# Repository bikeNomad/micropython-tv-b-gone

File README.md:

# MicroPython TV-B-Gone clone
## Introduction
This is a MicroPython implementation of the TV-B-Gone project.
The [TV-B-Gone](https://www.tvbgone.com/) (by Mitch Altman) is a universal remote control that can turn off most televisions.
Unfortunately, the existing open-source implementations (for the ATTiny microcontrollers) have very outdated code databases and don't work with many modern TVs.
This project is designed to work with the ESP32 microcontroller and a recent version of MicroPython (I used v1.25.0).
I wanted to use the ESP32 because its RMT peripheral allows for simple and well controlled modulated IR signal generation.
## Testing status
Currently this code has been tested and works fine with ESP32-S3 boards.
I am currently using an Unexpected Maker TinyS3.
I started with a XIAO ESP32-C6 board, but found that the `deepsleep()` had issues.
## Development Workflow
I didn't want to spend lots of time editing codes, so I bought a [very cheap IR universal remote control from Amazon](https://www.amazon.com/dp/B0D6GFNFJY).
I asked Google Gemini to tell me the top 10 brands of modern TVs and collected the power-toggle codes for every code given in my universal remote manual for the 10 brands, using an IR receiver module connected to my Saleae Logic 8 logic analyzer.
Saleae's automation API and Python helped me automate the collection process.
Then I had the Cody AI write a Python script that could read the CSV files produced by the Saleae logic analyzer and convert them into a format that could be used by the ESP32. Along the way I also had it identify the IR protocols, and also produce hex representations of the codes for recognized protocols, to allow me to eliminate duplicate codes.
## TV Brands Supported
The following brands are supported (30 separate codes):
  - Samsung
  - LG
  - TCL
  - Hisense
  - Sony
  - Vizio
  - Panasonic
  - Philips
  - Sharp
  - Toshiba
  - Hitachi
  - ONN
  - Mitsubishi
## Installation and usage
Copy all the files from the `firmware` directory to your ESP32's root directory.
After a reset, the ESP32 will send all the codes and will go into deep sleep until the button is pressed.
When the button is pressed, the ESP32 will wake up and start sending IR codes.
## Capturing new codes
If you want to capture new codes, get into the MicroPython REPL and hit Ctrl-C in the 3 seconds after the codes are sent.
After you have quit capturing codes, the ESP32 will will be ready to send the codes you entered
the next time you push the button.
## Code structure
The representation of each of the codes in `firmware/codes.py` is a tuple with periods in microseconds. Each code may have an optional name as a string as the first member of the tuple.
I used the universal remote's own code numbers as the names.
This is the same representation as the captured codes in the `captured` directory.
## Configuration
See [`firmware/config.py`](firmware/config.py) for the configuration options.
### Circuit-related configuration
  - `OUTPUT_PIN` is the GPIO pin used for the IR LED.
  - `ACTIVE_LEVEL` is the level that the output pin will be set to when the IR LED is active. For an output circuit that uses an NPN or NMOS transistor, this should usually be 1 (high).
  - `BUTTON_PIN` is the GPIO pin used for the button. I used the GPIO that is connected to the `BOOT` button on my development board. This pin should be one of the GPIO pins that is connected to the RTC and can be used for deep sleep wakeup.
  - `BUTTON_ACTIVE_LEVEL` is the level that the button pin will be set to when the button is pressed. I used 0 (low) for my circuit, but some circuits may require a high level.
  - `BUTTON_PULL` is the pull-up or pull-down setting (if any) to use for the button pin. This can be `None`, `Pin.PULL_UP`, or `Pin.PULL_DOWN`.
  - `RGB_LED_PIN` is the GPIO pin used for the RGB LED. I used GPIO 48, because it was connected to the onboard RGB LED on my development board. If you don't have an RGB LED, you can set this to `None` to disable the RGB LED.
  - `RGB_LED_POWER_PIN` is the GPIO pin used to power the RGB LED, if any. This is used on the TinyS3. Use `None` if you don't have such a power pin.
  - `USER_LED_PIN` is the GPIO pin used for the monochrome LED. If you don't have a monochrome LED, you can set this to `None` to disable the monochrome LED.
  - `USER_LED_ACTIVE_LEVEL` is the level that the monochrome LED pin should be set to to turn the LED is on.
  - `DUTY_CYCLE` is the duty cycle to use for the IR LED.
  This is the percentage of time that the IR LED will be on during the 38kHz pulses.
  I used 25% for my circuit, but numbers from 10% to 50% should work. 25% is a good starting point.
  - `INPUT_PIN` is the (optional) GPIO pin used for the IR receiver module. I used GPIO 4, but you can use any GPIO pin that is not used for other purposes.
  - `INPUT_ACTIVE_LEVEL` is the level that the input pin will be set to when the IR receiver is receiving a signal. This is usually 0.
  - `INPUT_POWER_PIN` is the (optional) GPIO pin used to power the IR receiver module (instead of just connecting it to 3.3V).
  `None` means the IR receiver is not used or is powered from 3.3V.
  - `USE_XAIO_ESP32C6` is a boolean that determines whether to use the XIAO ESP32-C6 board as the default for ESP32-C6 builds.
  If you have a different ESP32-C6 board, you should set this to `False`.
  
You can also edit the RGB LED colors in `firmware/config.py` if you want different colors.
## Transmitter Circuit Design
You will need a 940nm IR LED and a simple one-transistor driver circuit to drive the LED.
See Peter Hinch's explanation [here](https://github.com/peterhinch/micropython_ir/blob/master/TRANSMITTER.md).
Although Peter's examples show an NPN BJT transistor, 
I used a VN3205 N-channel MOSFET transistor because I had one and it has a very low on resistance (Rds(on) rating of 0.4 ohm),
but any logic-level (Vgs(th) < 3V) N-channel MOSFET should work.
The higher the Rds(on) rating, the lower the IR output will be.
The IR LED's cathode is connected to the drain of the transistor,
and its anode is connected in series with a current limiting resistor whose other end is connected to your highest-voltage power rail (I used +5V on the dev board, and VBAT on the portable device).
The MOSFET's source is connected to ground, and its gate is connected to the GPIO pin used for the IR LED.
Note that if you are using a battery, the voltage will probably be lower than 5V, so you may need to adjust the resistor value accordingly.
Also the IR output will be reduced as the battery voltage drops if you use a simple one-transistor circuit with no provisions for constant-current output.
The value of the current limiting resistor depends on the power supply voltage and the IR LED's maximum pulse current rating.
Figure the resistor value using Ohm's law: R = (Vsupply - Vled - Vsat) / Iled.
Vled is the forward voltage drop of the IR LED (typically around 1.2-1.5V),
Vsat is the saturation voltage of the transistor (typically around 0.1V for an NPN), and Iled is the desired current through the IR LED.
If you're using a MOSFET, Vsat would be Iled*Rds(on), where Rds(on) is the on-resistance of the MOSFET.
I used a high-power IR LED with a maximum pulse current rating of 200mA (TSAL6200), so I used a 22 ohm resistor to produce 100mA current pulses at 3.6V.

3.6V (battery) - 1.2V (LED) - (0.1 A * 0.4 ohm)) / 0.1 A = 23.6 ohm.

## Receiver Circuit Design
You will need an IR receiver module.
I used a 38kHz TSOP38238 IR receiver module, which is a common and cheap module.
Connect its power supply to +3.3V (or to `INPUT_POWER_PIN` if you are using one) and its ground to GND.
Connect its output pin to the `INPUT_PIN` GPIO on your ESP32.

## Files in this repository
  - [`analyze_signal.py`](analyze_signal.py): Analyzes a recorded IR signal and prints the results (mostly written by the Cody AI).
  - [`capture_saleae.py`](capture_saleae.py): Captures IR signals using Saleae Logic 2 and saves the data to a CSV file.
  - [`prompt_captures.py`](prompt_captures.py): A script to capture IR codes using the Saleae and save them to CSV files.
  - [`firmware/config.py`](firmware/config.py): Configuration file for the firmware.
  - [`firmware/codes.py`](firmware/codes.py): IR codes for the ESP32.
  - [`firmware/main.py`](firmware/main.py): Main firmware file.
  - [`firmware/capture.py`](firmware/capture.py): Captures IR codes using the ESP32 and saves them to a Python file.
  - [`firmware/leds.py`](firmware/leds.py): RGB and monochrome LED control code.
  - [`firmware/xiao_esp32c6.py`](firmware/xiao_esp32c6.py): Seeed Studio XIAO ESP32-C6 board support.
  - [`firmware/code_compare.py`](firmware/code_compare.py): Compares all the IR codes and prints similar pairs.
  - `good/`: CSV files of good (non-duplicated) IR codes captured using the Saleae Logic.
  - `good_py/`: Good IR codes captured using the Saleae Logic, converted to Python format.
  - `README.md`: This file.
  - [`docs/irmp_protocols.csv`](docs/irmp_protocols.csv): A CSV file with details of IR protocols supported by the IRMP library.
  - [`hardware/`](hardware/): Hardware design files.
## External references
  - [TV-B-Gone](https://www.tvbgone.com/)
  - [MicroPython IR library](https://github.com/peterhinch/micropython_ir/)
  - [IRMP project](https://github.com/IRMP-org/IRMP)
  - [Ken Shirrif's Arduino TV-B-Gone](https://github.com/shirriff/Arduino-TV-B-Gone)
  - [Adafruit's TV-B-Gone kit](https://github.com/adafruit/TV-B-Gone-kit)
## Pictures of my device

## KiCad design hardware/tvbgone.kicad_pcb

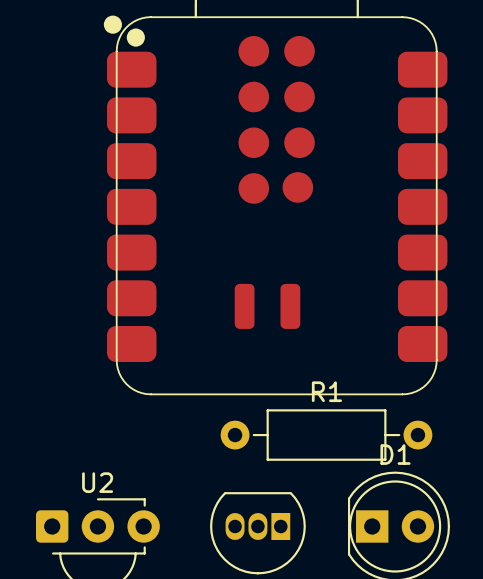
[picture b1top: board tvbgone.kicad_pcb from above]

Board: 2 copper layers, 5 parts (0 on the bottom side), 7 nets, no tracks yet.

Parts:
D1: TSAL6200; LED_D5.0mm_IRGrey
Q1: BS170; TO-92_Inline
R1: 22; R_Axial_DIN0207_L6.3mm_D2.5mm_P10.16mm_Horizontal
U1: XIAO-ESP32-S6; XIAO-ESP32C6-SMD
U2: TSOP382xx; Vishay_MINICAST-3Pin

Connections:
+3.3V: U1.12 (3V3), U2.3 (Vs)
+BATT: R1.1, U1.14 (5V)
GND: Q1.3 (S), U1.13 (GND), U2.2 (GND)
IR_IN: U1.2 (GPIO1_A1_D1), U2.1 (OUT)
IR_OUT: Q1.2 (G), U1.1 (GPIO0_A0_D0)
unnamed: D1.2 (A), R1.2
unnamed: D1.1 (K), Q1.1 (D)

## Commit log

2025-05-18 Improved
2025-05-18 Added capture
2025-05-18 edits
2025-05-19 Added captures and python files
2025-05-19 Got FW working
2025-05-19 Round for more accuracy
2025-05-19 Simplified.
2025-05-19 added output message at start
2025-05-19 Add code number to signals.py and REPL output.
    Also add Seiki 5751 code for testing.
2025-05-19 Correct for codes with names
2025-05-19 Add comments and blink LED.
    Also rename signals.py as codes.py
2025-05-19 Reduce blue blink time to 50ms
2025-05-19 Add list of TV brands
2025-05-19 Add tv-b-gone link
2025-05-20 WIP: added input capture
2025-05-20 WIP: adding ESP32-C6
2025-05-20 WIP: add hardware design info
2025-05-20 Added loading of captured codes.
    Also move button to GPIO 2.
2025-05-21 Add deepsleep() support.
    Also allow getting into capture from main loop by Ctrl-C.
    Also add support for INPUT_POWER_PIN.
    Also add PDF schematic.
2025-05-21 Working on getting deepsleep() to work. Still broken on ESP32-C6 but probably works with other chips.
2025-05-21 Add support for UM TinyS3 (including RGB_POWER_PIN)
2025-05-21 Add support for UM TinyS3
2025-05-21 Add code comparison; remove duplicated codes.
2025-05-21 add __pycache__ to .gitignore
2025-05-21 Added images of finished device
2025-05-22 added some more codes.
2025-05-22 add some codes
2025-05-22 Removed some duplicate codes
2025-05-23 Add Mitsubishi codes.
    Also change transistor to VN3205 and add docs.
2025-05-31 WIP: chasing down too-high (360µA) deep-sleep current
